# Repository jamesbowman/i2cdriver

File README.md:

I2CDriver is a tool for controlling any I2C device from your PC's USB port,
and can also monitor and capture I2C traffic.
It connects as a standard USB serial device, so there are no drivers to install.
On the main site
[i2cdriver.com](https://i2cdriver.com),
there are drivers for

* Windows/Mac/Linux GUI
* Windows/Mac/Linux command-line
* Python 2 and 3
* Windows/Mac/Linux C/C++

Full documentation is at
[i2cdriver.com](http://i2cdriver.com).

For developers: How to make a release
-------------------------------------

To release Python:

    cd python3
    rm -rf dist/*
    python -m build
    twine check dist/*
    twine upload dist/*

To build the Windows installer, you first need to build the two executables
``i2ccl.exe`` and ``i2cgui.exe`` then use an NSIS script to create the installer.

On Linux cross-compile ``i2ccl``:
  
    cd c
    make -f win32/Makefile

On Windows first make sure that you can run the GUI on the command-line, e.g.

    python python\samples\i2cgui.py

(You may need to install i2cdriver, wxPython and pySerial).

Then build the GUI executable using ``pyinstaller``:

    cd python\samples
    pyinstaller --onefile --windowed --icon=../../images/i2cdriver.ico i2cgui.py

This builds the executable in ``python\samples\dist\i2cgui.exe``.

The Windows installer is built with NSIS (Nullsoft Scriptable Install System). Download and install it.

Copy the two executables ``i2ccl.exe`` and ``i2cgui.exe`` into ``nsis/``.

Then build the installer with NSIS:

    cd nsis
    "C:\Program Files\NSIS\makensis.exe" i2cdriver.nsi

The script ``go.bat`` in ``nsis`` has an example complete flow.

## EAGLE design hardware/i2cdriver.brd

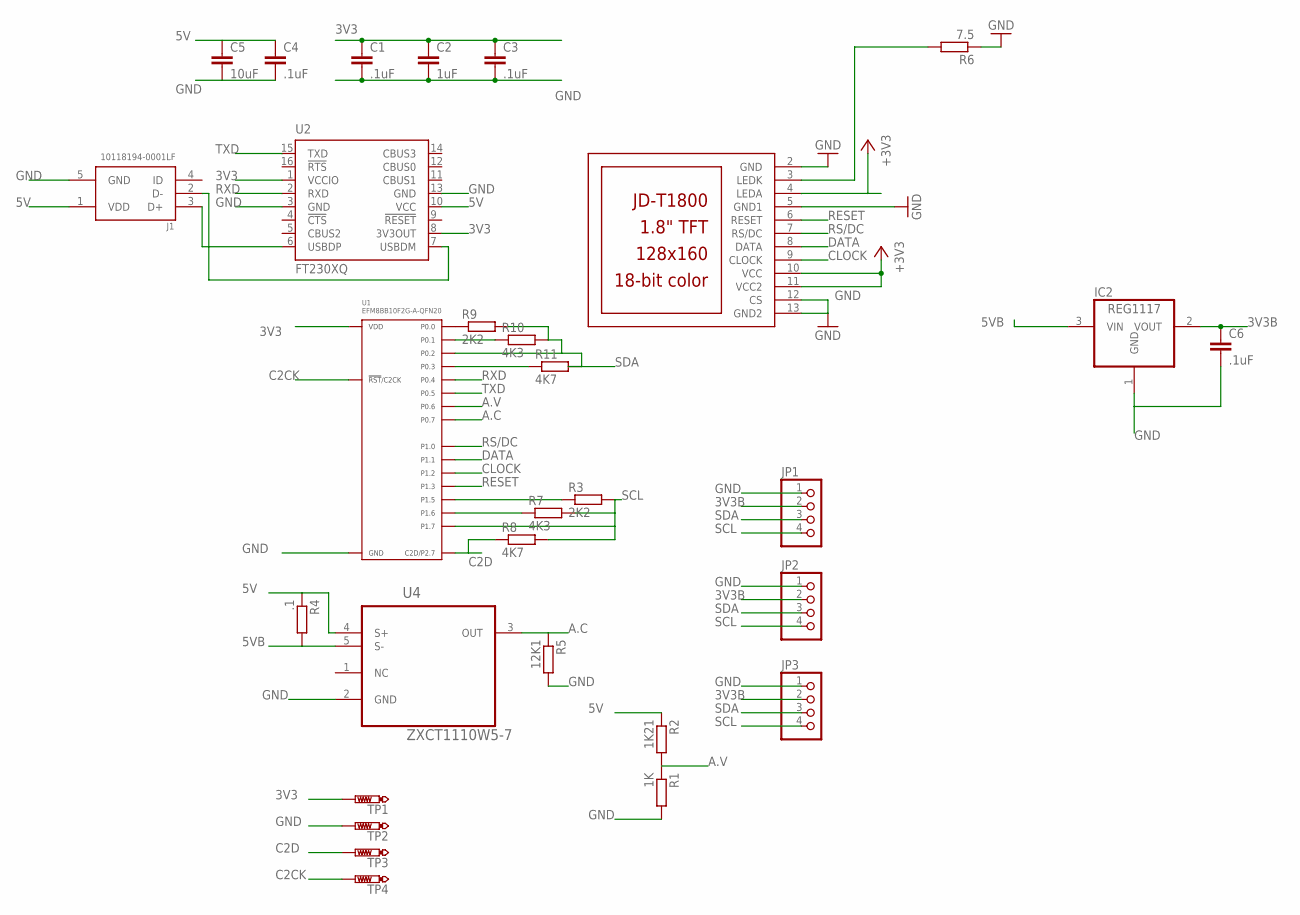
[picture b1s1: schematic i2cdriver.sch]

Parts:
C1, C3, C4, C6: .1uF; C0402K
C2: 1uF; C0402K
C5: 10uF; C0402K
IC2: REG1117; SOT223
J1: 10118194-0001LF; FRAMATOME_10118194-0001LF
JP1, JP2, JP3: PINHD-1X4/90; 1X04/90
R1: 1K; R0402
R2: 1K21; R0402
R3, R9: 2K2; R0402
R4: .1; R0805
R5: 12K1; R0402
R6: 7.5; R0402
R7, R10: 4K3; R0402
R8, R11: 4K7; R0402
TP1, TP2, TP3, TP4: PTR1B1,27; B1,27
U1: EFM8BB10F2G-A-QFN20; EFM8BB10F(2/4/8)G-A-QFN20; MPN EFM8BB10F2G-A-QFN20
U2: FT230XQ; QFN16
U4: ZXCT1110W5-7; SOT95P280X130-5N
U$1: JD-T1800

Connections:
3V3: C1.1, C2.1, C3.1, TP1.TP, U1.P$4 (VDD), U2.1 (VCCIO), U2.8 (3V3OUT), U$1.4 (LEDA), U$1.10 (VCC), U$1.11 (VCC2)
3V3B: C6.1, IC2.2 (VOUT), JP1.2, JP2.2, JP3.2
5V: C4.1, C5.1, J1.1 (VDD), R2.1, R4.1, U2.10 (VCC), U4.4 (S+)
5VB: IC2.3 (VIN), R4.2, U4.5 (S-)
A.C: R5.1, U1.P$15 (P0.7), U4.3 (OUT)
A.V: R1.1, R2.2, U1.P$16 (P0.6)
C2CK: TP4.TP, U1.P$5 (!RST!/C2CK)
C2D: R8.1, TP3.TP, U1.P$6 (C2D/P2.7)
C2D1: R11.1, U1.P$19 (P0.3)
CLOCK: U1.P$11 (P1.2), U$1.9 (CLOCK)
DATA: U1.P$13 (P1.1), U$1.8 (DATA)
GND: C1.2, C2.2, C3.2, C4.2, C5.2, C6.2, IC2.1 (GND), J1.5 (GND), JP1.1, JP2.1, JP3.1, R1.2, R5.2, R6.1, TP2.TP, U1.P$3 (GND), U1.P$12 (GND), U1.PAD (GND), U2.3 (GND), U2.13 (GND), U4.2 (GND), U$1.2 (GND), U$1.5 (GND1), U$1.12 (CS), U$1.13 (GND2)
unnamed: R10.1, U1.P$1 (P0.1)
unnamed: R7.1, U1.P$7 (P1.6)
unnamed: R3.1, U1.P$8 (P1.5)
unnamed: R6.2, U$1.3 (LEDK)
unnamed: R9.1, U1.P$2 (P0.0)
unnamed: J1.3 (D+), U2.6 (USBDP)
unnamed: J1.2 (D-), U2.7 (USBDM)
RESET: U1.P$10 (P1.3), U$1.6 (RESET)
RS/DC: U1.P$14 (P1.0), U$1.7 (RS/DC)
RXD: U1.P$18 (P0.4), U2.2 (RXD)
SCL: JP1.4, JP2.4, JP3.4, R3.2, R7.2, R8.2, U1.P$9 (P1.7)
SDA: JP1.3, JP2.3, JP3.3, R9.2, R10.2, R11.2, U1.P$20 (P0.2)
TXD: U1.P$17 (P0.5), U2.15 (TXD)

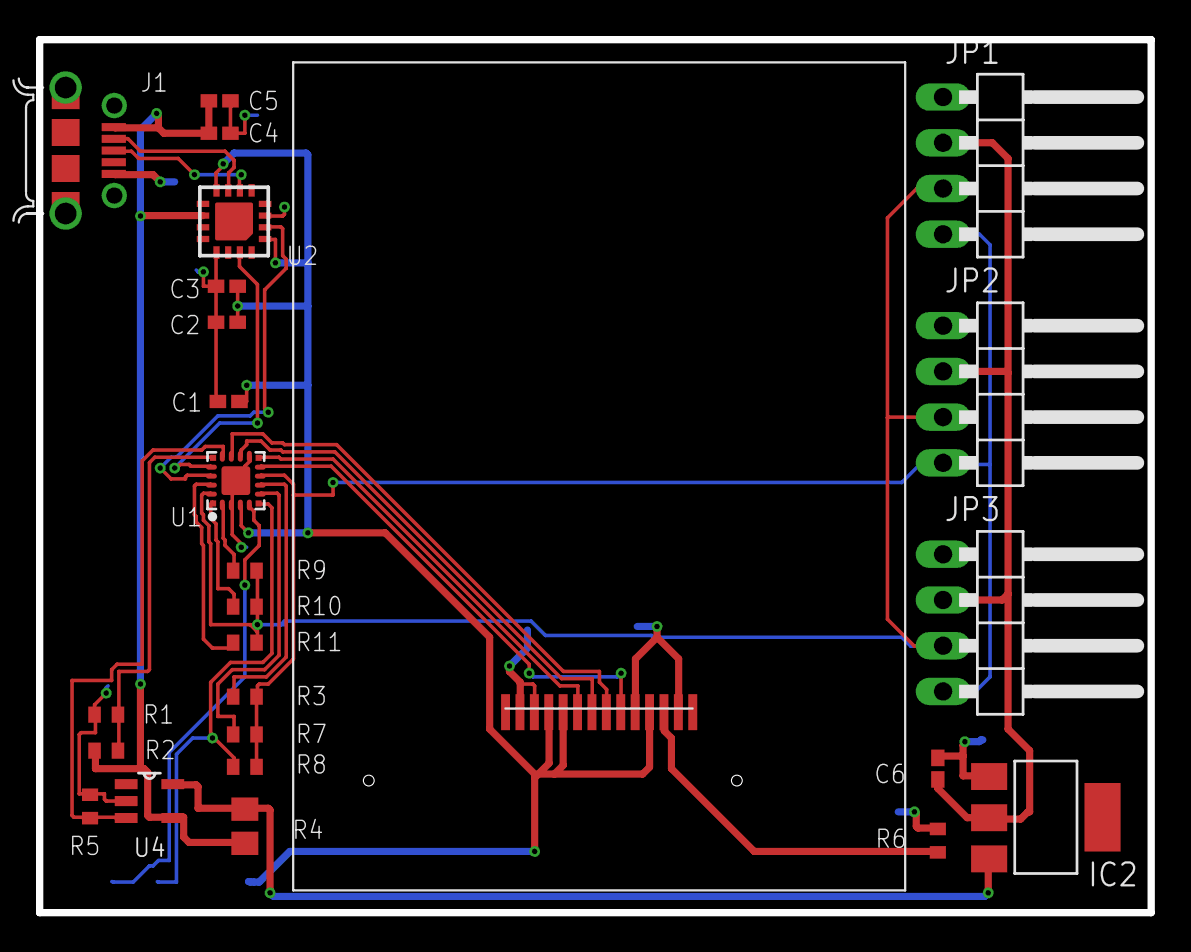
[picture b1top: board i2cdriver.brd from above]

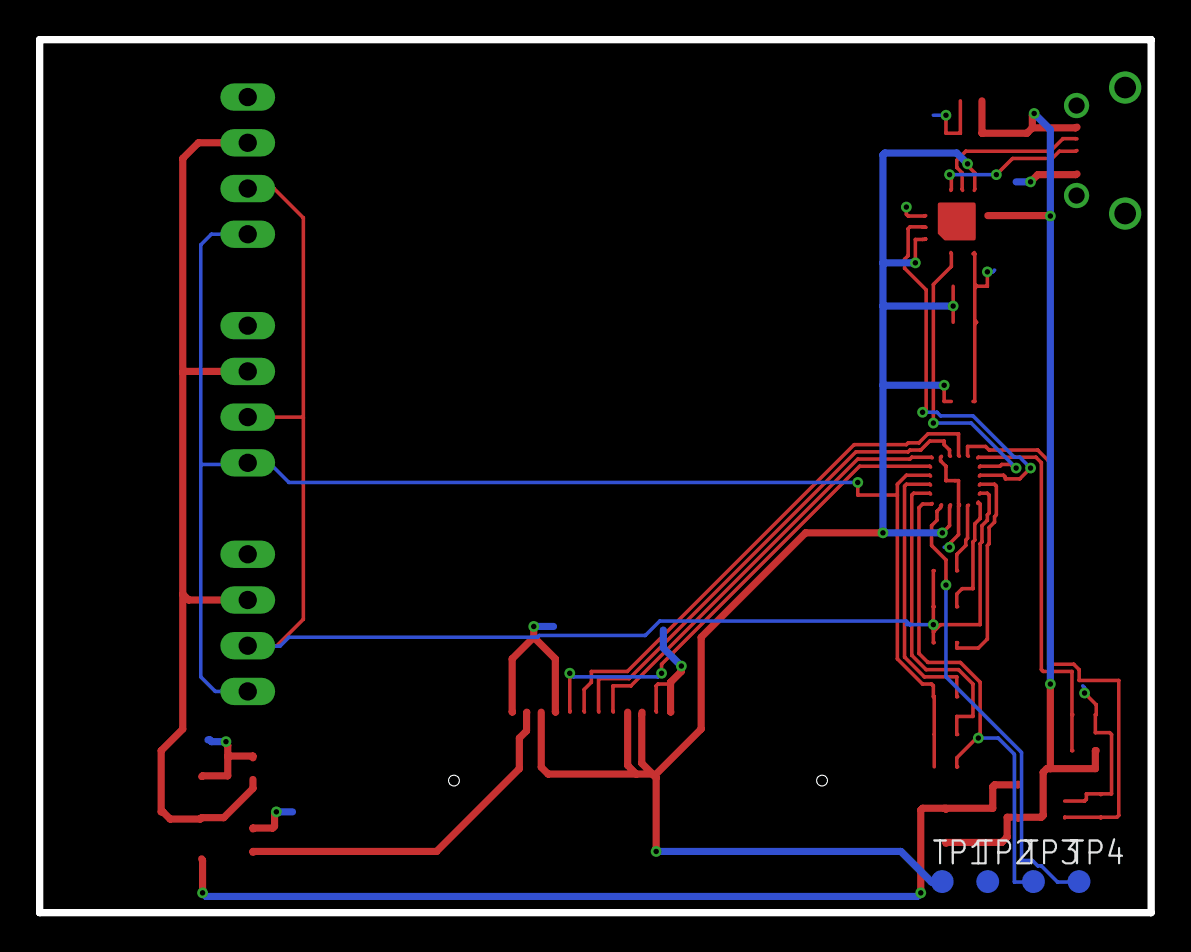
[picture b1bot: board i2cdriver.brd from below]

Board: 2 copper layers, 61.7 x 48.5 mm, 30 parts (4 on the bottom side), 25 nets.

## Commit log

2019-02-10 Firmware initial import
2019-02-10 import PCB design
2019-02-10 READMEs, images, travis stub
2019-02-10 BSD 3-clause
2019-02-12 Start of Python import
2019-02-20 initial import of main module
2019-02-20 First sample
2019-02-21 Sample for EDS LED part
2019-02-21 DIG2, BEEP, EPROM samples
2019-02-21 clock sample
2019-02-21 EDS CLOCK class and sample, using datetime
2019-02-22 Enable Travis for Python
2019-02-23 Skeleton of C library
2019-02-23 C API first cut, i2ccl running
2019-02-23 Monitor mode in C API and i2ccl
2019-02-24 Test case builds i2ccl
2019-02-24 Add EDS-IR sample, EDS-take-a-ticket sample
2019-02-24 sample for the POT, and an egg-timer app
2019-02-24 Add proper comment to egg timer
2019-02-24 Consistent case for CLOCK
2019-02-24 Add COMPASS code and sample, color compass app
2019-02-25 ACCEL class and sample
2019-02-25 i2cgui now has heat map and monitor mode button
2019-02-25 Clean up a little
2019-02-25 Clean up comments
2019-02-25 Fix custom baud rate for termios on apple
2019-02-26 Compile with -Wall, clean up all warnings. #1
2019-02-27 win32 Makefile for i2ccl.exe
2019-03-01 Fixed GridFlex error Fixed reg-ex for os x serial port selection
2019-03-02 Raduio buttons for i2c device
2019-03-02 Add write/read/stop buttons
2019-03-02 Make monitor mode a ToggleButton
2019-03-02 I2C reset button
2019-03-03 Speed control, 100 or 400 kHz
2019-03-03 regwr accepts tuples properly. Fix EDS.LED for Python 2
2019-03-03 Version bump to 0.0.2
2019-03-03 Properly do port enumeration on Windows
2019-03-03 Windows icon
2019-03-03 NSIS install script, win32 port enumeration in GUI
2019-03-03 Better notes on releasing
2019-03-04 LED 8x8 example
2019-03-04 Bi-Color (Red/Green) 24-Bar Bargraph
2019-03-04 OLED 128x64 module from DIYMall
2019-03-04 MPR121 touch detection
2019-03-04 Sparkfun's Qwiic joystick and keypad
2019-03-04 remove debug
2019-03-04 Checkpoint, have "HELLO WORLD"
2019-03-04 Clean up timing, remove debug
2019-03-04 BNO080 IMU sample
2019-03-04 Sparkfun MAG3110 3D Magnetometer
2019-03-08 Update README.md
    Fix link for #8
2019-03-10 Decrease grid spacing so gui fits on Windows screen 768 pixels high [#11]
2019-03-10 Clearer instructions on how to build the Windows release. #9
2019-03-10 Bump version to 0.0.4
2019-03-10 improve Windows build instructions
2019-03-10 Update README.md
    Be more explicit about running i2cgui #9
2019-03-17 TEMP sample
2019-03-18 i2cgui now accepts a port on the command-line [#9]
2019-03-18 Catch exceptions and display in a dialog box
2019-03-22 Better handling of device fails
2019-03-23 Fix device range to be 08-77
2019-03-29 Clean up handling of selected device when it appears/disappears from network #12
2019-04-03 First cut of pullup control [#7]
2019-04-03 Clean up pullups control handling. [#7]
2019-04-25 Remove unused modules
2019-04-25 Sphinx doc set up
2019-04-26 i2cgui installed as a script, version bump to 0.0.5
2019-04-29 Capture example
2019-04-29 Capture to CSV file implemented in GUI #13
2019-04-29 Clean up
2019-05-11 Code changes for MSVC as suggested [#16]
2019-05-11 changes for MSVC
2019-05-11 added function to set i2c start bit to public API
2019-09-10 Instantiate GridSizer() in a way that works on both Wx 3. and 4.
    Looks like GridSizer.SetHGap() and SetVGap() have no effect on Wx 3.
    But at least now it doesn't crash on Wx 3.
2019-09-10 Version bump to 0.0.6
2019-09-10 Fix EDS DIG2 raw method
2020-01-04 setspeed() and setpullups() now update their respective variables
    [#27]
2020-01-04 Version 0.0.7
2020-01-04 Slow down remote controll polling
2020-01-07 Acceptance test for i2cdriver and i2cmini firmware
2020-01-08 Correctly hangle regrd with count of 256 or greater.
    [#28]
2020-01-08 Version 0.0.8
2020-01-14 all tests now passing on Python 2.7
2020-01-16 Sphinx doc first cut
2020-01-21 Add 'x' command (bus reset) to C common header and i2ccl.
    [#30]
2020-01-26 Proper busy bus expection
2020-01-26 Adds to PATH on install, removes on uninstall Using recommended functions at https://nsis.sourceforge.io/Path_Manipulation
    [#29]
2020-02-19 Add example using a TCA9548A I2C switch
2020-03-06 Fix cast for clang/clang++ in -c++17 mode, using a C-style cast so it's buildable by plain C users.
    Add Makefile.clang
    Add regression test for Travis
    [#39]
2020-03-06 Add capture mode support to API and i2ccl
2020-03-06 Don't do a device scan when bus is blocked. Properly handle capture file cancel path.
2020-03-16 PCA9685 sample
2020-03-19 Fix up typos
2020-05-19 Nontendo wii classic controller interface
2021-02-10 Remove old doc skeleton
2021-02-10 rtd attempt
2021-02-10 docs build requires pyserial
2021-02-10 Use index.rst
2021-02-10 rtd requirements explicit
2021-02-10 Explicit package install
2021-02-10 yaml whitespace fix?
2021-02-10 requirements.txt not needed
2021-02-10 add image
2021-02-10 Link to main site
2021-02-10 Reword
2021-02-11 Generate all formats
2021-02-11 Version bump to 1.0.0
2021-02-12 Readthedocs badge
2022-02-05 BM390 sample, by Adafruit
2023-02-07 Fix link
2024-05-22 Added i2c_disconnect to c sdk
    * Added closeSerialPort() for Linux build
    * i2c_disconnect() closes the serial port, and resets the `connected` flag to zero.
2024-06-05 feat(i2c): add baud rate setting functionality
    Add a new function `i2c_setbaud` allowing the baud rate of the I2C connection to be set. This feature provides the ability to configure the communication speed to standard values (100kbps or 400kbps)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
2025-03-12 refactor(i2cgui): use daemon parameter in Thread initialization
    Simplified the creation of the threading.Thread by utilizing the 'daemon' keyword argument directly during instantiation. This enhances code readability and aligns with modern Python practices. The f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
2025-04-05 Run on every commit
2025-04-05 Remove Python tests
2025-04-05 Skip requirements.txt
2025-04-05 Rewrite i2c_setbaud() as i2c_setspeed()
2025-04-07 New python release
2025-04-07 Smoke test Python install
2025-04-07 Samples included
2025-06-30 Version bump
2025-07-21 Tiny Code Reader
2025-09-08 Fix broken EDS LED, using old regwr() method
2025-09-08 Fix EDS LED
2025-09-08 Fix build instructions
